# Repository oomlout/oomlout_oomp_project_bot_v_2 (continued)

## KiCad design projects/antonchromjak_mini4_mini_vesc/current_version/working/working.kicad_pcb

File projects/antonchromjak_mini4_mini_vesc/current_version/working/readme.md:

# mini4
 
## summary 
* id: antonchromjak_mini4_mini_vesc
* user: antonchromjak
* name: mini4
* board: mini_vesc
* repo: https://github.com/antonchromjak/MINI4
* src_file_repo_kicad_pcb: MINI VESC.kicad_pcb
* src_file_repo_kicad_pcb_link: https://github.com/antonchromjak/MINI4/tree/master/MINI VESC.kicad_pcb

* src_file_repo_sch: MINI VESC.sch
* src_file_repo_sch_link: https://github.com/antonchromjak/MINI4/tree/master/MINI VESC.sch
* full details link: https://github.com/oomlout/oomlout_oomp_project_bot_v_2/tree/main/projects/antonchromjak_mini4_mini_vesc/current_version/working  

## schematic  
  
[schematic (pdf)](working_schematic.pdf) 

## pcb  

[board (pdf)](working.pdf)  

## working_bom
| Id | Designator | Footprint | Quantity | Designation | Supplier and ref |  | None | 
| --- | --- | --- | --- | --- | --- | --- | --- | 
| 1 | U4,U5,U6 | MSOP | 3 | AD8418 |  |  | [''] | 
| 2 | C9,C10,C11,C17,C21,C77,C78,C22,C29,C6,C7,C8,C18,C19,C26,C27,C86,C87,C88,C89,C90 | C_0603 | 21 | 2u2 |  |  | [''] | 
| 3 | C14,C15,C16 | C_0603 | 3 | 4n7 |  |  | [''] | 
| 4 | R4,R12,R14,R16 | R_0603 | 4 | 25k5 |  |  | [''] | 
| 5 | R5,R13,R15,R17 | R_0603 | 4 | 2k2 |  |  | [''] | 
| 6 | R18,R19,R20,R30 | R_0603 | 4 | 100R |  |  | [''] | 
| 7 | C23 | R_0603 | 1 | 220nF |  |  | [''] | 
| 8 | C24,C25,C12,C13,C48,C28,C39,C60,C61,C62,C4,C5,C32,C63,C74,C75,C79,C82,C84,C85 | R_1206 | 20 | 10u |  |  | [''] | 
| 9 | D1 | D_SOD-123 | 1 | D_Schottky |  |  | [''] | 
| 10 | R21 | R_0603 | 1 | 510R |  |  | [''] | 
| 11 | R22 | R_0603 | 1 | 8k |  |  | [''] | 
| 12 | U8 | SOT-23-6 | 1 | LMR16006 |  |  | [''] | 
| 13 | P9,P10,P11 | JST_ZH_1.5_6-Pin | 3 | CONN_01X06 |  |  | [''] | 
| 14 | D3,D4 | R_0603 | 2 | LED |  |  | [''] | 
| 15 | R28,R29 | R_0603 | 2 | 220R |  |  | [''] | 
| 16 | C30,C31 | C_0603 | 2 | 10pF |  |  | [''] | 
| 17 | X1 | 5x3.2KRISTALL | 1 | CRYSTAL_SMD |  |  | [''] | 
| 18 | C34,C40,C42,C44,C45,C46,C47,C49,C50,C51,C52,C53,C54,C55,C56,C57,C58,C59,C64,C68,C69,C70,C71,C72,C73,C35,C36,C33,C37,C38,C41,C43,C65,C66,C67,C80,C81,C83 | R_1206 | 38 | C |  |  | [''] | 
| 19 | P1,P2,P3,P4,P5,P6 | prekov | 6 | CONN_1 |  |  | [''] | 
| 20 | R31,R33,R34 | R_0603 | 3 | 10k |  |  | [''] | 
| 21 | R32 | R_0603 | 1 | 10kNTC |  |  | [''] | 
| 22 | Q2,Q4,Q6,Q1,Q3,Q5 | DFN5 | 6 | Q_NMOS_GSD |  |  | [''] | 
| 23 | L1 | WE-MAPI | 1 | 22uH |  |  | [''] | 
| 24 | C1,C2,C3 | C_0603 | 3 | 220n |  |  | [''] | 
| 25 | U7 | lqfp64_pad_mod | 1 | STM32F40X_LQFP64 |  |  | [''] | 
| 26 | C20 | C_0603 | 1 | 220nF |  |  | [''] | 
| 27 | R6,R7,R8,R9,R10,R11 | R_0603 | 6 | 7R5 |  |  | [''] | 
| 28 | R25,R27 | R_0603 | 2 | 22R |  |  | [''] | 
| 29 | C76 | R_0603 | 1 | 100n |  |  | [''] | 
| 30 | U1,U2,U3 | WSON10_ | 3 | LM5113 |  |  | [''] | 
| 31 | R1,R2,R3 | 2512Rv2 | 3 | RSENS |  |  | [''] | 
| 32 | U9,U10 | SOT-23 | 2 | MCP1700 |  |  | [''] | 

## bom_schematic
| Ref | Qnty | Value | Cmp name | Footprint | Description | Vendor | DNP | 
| --- | --- | --- | --- | --- | --- | --- | --- | 
| L1 | 1 | Wurth Electronics 74438335220 | INDUCTOR-RESCUE-MINI_VESC | mojaKniznica:WE-MAPI |  |  |  | 
| P1, P2, P3, P4, P5, P6 | 6 | CONN_1 | CONN_1-RESCUE-MINI_VESC | kicad_subory:prekov |  |  |  | 
| R1, R2, R3 | 3 | R0005 | RSENS-RESCUE-MINI_VESC | mojaKniznica:2512Rv2 |  |  |  | 
| U1, U2, U3 | 3 | LM5113SDE | LM5001-RESCUE-MINI_VESC | kicad_subory:WSON10__ |  |  |  | 
| U4, U5, U6 | 3 | AD8417 | AD8418-RESCUE-MINI_VESC | kicad_subory:MSOP |  |  |  | 
| U7 | 1 | STM32F405RGT6 | STM32F40X_LQFP64-RESCUE-MINI_VESC | crf1:lqfp64_pad_mod |  |  |  | 
| U8 | 1 | LMR16006YDDCT | BD9G101G-RESCUE-MINI_VESC | TO_SOT_Packages_SMD:SOT-23-6 |  |  |  | 
| U9, U10 | 2 | MCP1700 | MCP1700-RESCUE-MINI_VESC | TO_SOT_Packages_SMD:SOT-23 |  |  |  | 
| X1 | 1 | ABM3B-8.000MHZ | CRYSTAL_SMD-RESCUE-MINI_VESC | mojaKniznica:5x3.2KRISTALL |  |  |  |

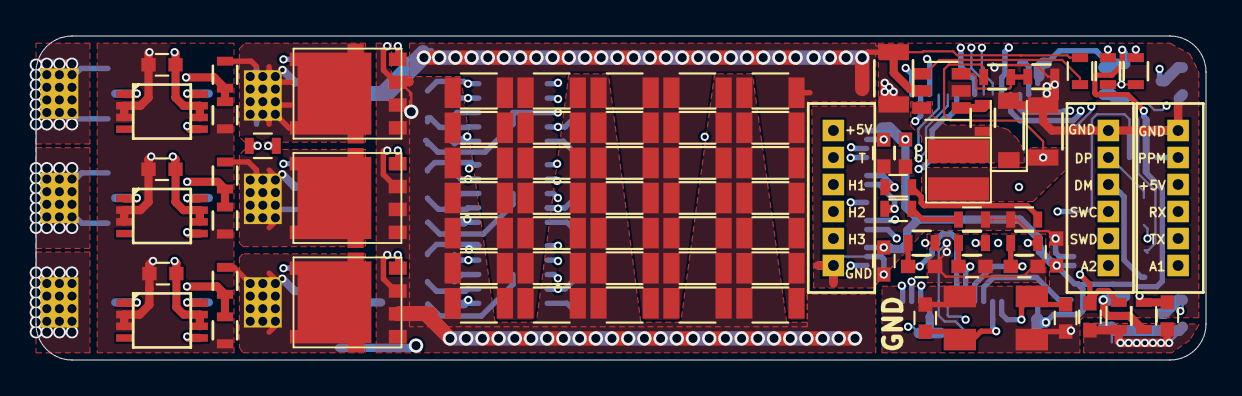
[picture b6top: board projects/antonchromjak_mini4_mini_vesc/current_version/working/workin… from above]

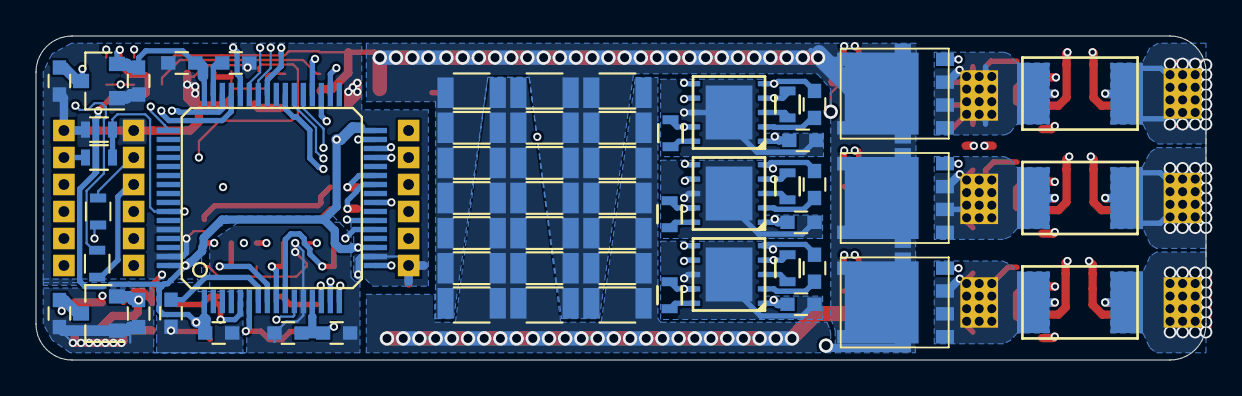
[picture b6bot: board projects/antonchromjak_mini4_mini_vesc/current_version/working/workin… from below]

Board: 4 copper layers, 65.0 x 18.0 mm, 151 parts (59 on the bottom side), 72 nets.

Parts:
C1, C2, C3: 220n; C_0603
C4, C5, C12, C13, C24, C25, C28, C32, C39, C48, C60, C61, C62, C63, C74, C75, C79, C82, C84, C85: 10u; R_1206
C6, C7, C8, C9, C10, C11, C17, C18, C19, C21, C22, C26, C27, C29, C77, C78, C86, C87, C88, C89, C90: 2u2; C_0603
C14, C15, C16: 4n7; C_0603
C20: 220nF; C_0603
C23: 220nF; R_0603
C30, C31: 10pF; C_0603
C33, C34, C35, C36, C37, C38, C40, C41, C42, C43, C44, C45, C46, C47, C49, C50, C51, C52, C53, C54, C55, C56, C57, C58, C59, C64, C65, C66, C67, C68, C69, C70, C71, C72, C73, C80, C81, C83: C; R_1206
C76: 100n; R_0603
D1: D_Schottky; D_SOD-123
D3, D4: LED; R_0603
L1: 22uH; WE-MAPI
P1, P2, P3, P4, P5, P6: CONN_1; prekov
P9, P10, P11: CONN_01X06; JST_ZH_1.5_6-Pin
Q1, Q2, Q3, Q4, Q5, Q6: Q_NMOS_GSD; DFN5
R1, R2, R3: RSENS; 2512Rv2
R4, R12, R14, R16: 25k5; R_0603
R5, R13, R15, R17: 2k2; R_0603
R6, R7, R8, R9, R10, R11: 7R5; R_0603
R18, R19, R20, R30: 100R; R_0603
R21: 510R; R_0603
R22: 8k; R_0603
R25, R27: 22R; R_0603
R28, R29: 220R; R_0603
R31, R33, R34: 10k; R_0603
R32: 10kNTC; R_0603
U1, U2, U3: LM5113; WSON10_
U4, U5, U6: AD8418; MSOP
U7: STM32F40X_LQFP64; lqfp64_pad_mod
U8: LMR16006; SOT-23-6
U9, U10: MCP1700; SOT-23
X1: CRYSTAL_SMD; 5x3.2KRISTALL

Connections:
+5V: C6.1, C7.1, C8.1, C25.2, C87.1, C89.1, L1.2, P9.1, P11.4, R22.1, U1.1, U2.1, U3.1, U9.3, U10.3
ADC_EXT1: P11.1, U7.21
ADC_EXT2: P10.1, U7.22
C1: C14.2, R18.2, U7.8
C2: C15.2, R19.2, U7.9
C3: C16.2, R20.2, U7.10
EN: R33.2, U8.4
HALL_1: P9.3, U7.37
HALL_2: P9.4, U7.38
HALL_3: P9.5, U7.39
HI1: U1.6, U7.41
HI2: U2.6, U7.42
HI3: U3.6, U7.43
I1: R18.1, U4.5
I2: R19.1, U5.5
I3: R20.1, U6.5
LED_GREEN: D3.2, U7.26
LED_RED: D4.2, U7.27
LI1: U1.7, U7.34
LI2: U2.7, U7.35
LI3: U3.7, U7.36
unnamed: C1.1, U1.2
unnamed: C2.1, U2.2
unnamed: C3.1, U3.2
unnamed: C17.2, U7.31
unnamed: C18.2, U7.47
unnamed: C20.2, U7.7
unnamed: C23.1, D1.1, L1.1, U8.6
unnamed: C23.2, U8.1
unnamed: C30.1, U7.5, X1.1
unnamed: C31.1, U7.6, X1.2
unnamed: C77.2, R31.2, R32.2, U7.17
unnamed: D3.1, R29.2
unnamed: D4.1, R28.2
unnamed: P1.1, R1.1, U4.1
unnamed: P2.1, R2.1, U5.1
unnamed: P3.1, R3.1, U6.1
unnamed: P10.4, R25.1
unnamed: P10.5, R27.1
unnamed: Q1.1, R6.1, U1.4
unnamed: Q2.1, R7.2, U1.9
unnamed: Q3.1, R8.1, U2.4
unnamed: Q4.1, R9.2, U2.9
unnamed: Q5.1, R10.1, U3.4
unnamed: Q6.1, R11.2, U3.9
unnamed: R6.2, U1.3
unnamed: R7.1, U1.10
unnamed: R8.2, U2.3
unnamed: R9.1, U2.10
unnamed: R10.2, U3.3
unnamed: R11.1, U3.10
unnamed: R21.2, R22.2, U8.3
RX: P11.3, U7.30
SENS_1: R12.1, R13.2, U7.14
SENS_2: R14.1, R15.2, U7.15
SENS_3: R16.1, R17.2, U7.16
SENS_SUPPLY: R4.2, R5.2, U7.11
SERVO: C76.2, R30.2, U7.58
SH1: C1.2, P4.1, Q1.2, Q2.3, R1.2, R12.2, U1.5, U4.8
SH2: C2.2, P5.1, Q3.2, Q4.3, R2.2, R14.2, U2.5, U5.8
SH3: C3.2, P6.1, Q5.2, Q6.3, R3.2, R16.2, U3.5, U6.8
SWCLK: P10.3, U7.49
SWDIO: P10.2, U7.46
TEMP_MOTOR: C78.2, P9.2, R34.2, U7.24
TX: P11.2, U7.29
USB-DM: R25.2, U7.44
USB-DP: R27.2, U7.45
VAA: C9.2, C10.2, C11.2, C19.1, C86.1, C90.1, R32.1, R34.1, U4.6, U4.7, U5.6, U5.7, U6.6, U6.7, U7.13, U10.2
VCC: C21.1, C22.1, C26.1, C27.1, C29.1, C88.1, U7.1, U7.19, U7.32, U7.48, U7.64, U9.2
VDD: C4.1, C5.1, C12.1, C13.1, C24.2, C28.1, C32.1, C33.1, C34.1, C35.1, C36.1, C37.1, C38.1, C39.1, C40.1, C41.1, C42.1, C43.1, C44.1, C45.1, C46.1, C47.1, C48.1, C49.1, C50.1, C51.1, C52.1, C53.1, C54.1, C55.1, C56.1, C57.1, C58.1, C59.1, C60.1, C61.1, C62.1, C63.1, C64.1, C65.1, C66.1, C67.1, C68.1, C69.1, C70.1, C71.1, C72.1, C73.1, C74.1, C75.1, C79.1, C80.1, C81.1, C82.1, C83.1, C84.1, C85.1, Q1.3, Q3.3, Q5.3, R4.1, R33.1, U8.5
VSS: C4.2, C5.2, C6.2, C7.2, C8.2, C9.1, C10.1, C11.1, C12.2, C13.2, C14.1, C15.1, C16.1, C17.1, C18.1, C19.2, C20.1, C21.2, C22.2, C24.1, C25.1, C26.2, C27.2, C28.2, C29.2, C30.2, C31.2, C32.2, C33.2, C34.2, C35.2, C36.2, C37.2, C38.2, C39.2, C40.2, C41.2, C42.2, C43.2, C44.2, C45.2, C46.2, C47.2, C48.2, C49.2, C50.2, C51.2, C52.2, C53.2, C54.2, C55.2, C56.2, C57.2, C58.2, C59.2, C60.2, C61.2, C62.2, C63.2, C64.2, C65.2, C66.2, C67.2, C68.2, C69.2, C70.2, C71.2, C72.2, C73.2, C74.2, C75.2, C76.1, C77.1, C78.1, C79.2, C80.2, C81.2, C82.2, C83.2, C84.2, C85.2, C86.2, C87.2, C88.2, C89.2, C90.2, D1.2, P9.6, P10.6, P11.6, Q2.2, Q4.2, Q6.2, R5.1, R13.1, R15.1, R17.1, R21.1, R28.1, R29.1, R31.1, U1.8, U2.8, U3.8, U4.2, U4.3, U5.2, U5.3, U6.2, U6.3, U7.12, U7.18, U7.60, U7.63, U8.2, U9.1, U10.1, X1.3
servoi: P11.5, R30.1

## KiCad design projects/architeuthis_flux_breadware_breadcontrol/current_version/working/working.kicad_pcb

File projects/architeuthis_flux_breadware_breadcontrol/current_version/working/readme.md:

# breadware
 
## summary 
* id: architeuthis_flux_breadware_breadcontrol
* user: architeuthis_flux
* name: breadware
* board: breadcontrol
* repo: https://github.com/Architeuthis-Flux/breadWare
* src_file_repo_kicad_pcb: v0.1-alpha/KiCad Files/BreadControl/BreadControl.kicad_pcb
* src_file_repo_kicad_pcb_link: https://github.com/Architeuthis-Flux/breadWare/tree/main/v0.1-alpha/KiCad Files/BreadControl/BreadControl.kicad_pcb
* src_file_repo_kicad_sch: Jumperless/Hardware/MTMatrixV3/MTMatrixV3.kicad_sch
* src_file_repo_kicad_sch_link: https://github.com/Architeuthis-Flux/breadWare/tree/main/Jumperless/Hardware/MTMatrixV3/MTMatrixV3.kicad_sch

* src_file_repo_sch: v0.1-alpha/KiCad Files/BreadControl/BreadControl.sch
* src_file_repo_sch_link: https://github.com/Architeuthis-Flux/breadWare/tree/main/v0.1-alpha/KiCad Files/BreadControl/BreadControl.sch
* full details link: https://github.com/oomlout/oomlout_oomp_project_bot_v_2/tree/main/projects/architeuthis_flux_breadware_breadcontrol/current_version/working  

## schematic  
  
[schematic (pdf)](working_schematic.pdf) 

## pcb  

[board (pdf)](working.pdf)  

## working_bom
| Id | Designator | Footprint | Quantity | Designation | Supplier and ref |  | None | 
| --- | --- | --- | --- | --- | --- | --- | --- | 
| 1 | C1 | C_0805_2012Metric_Pad1.15x1.40mm_HandSolder | 1 | 1uF |  |  | [''] | 
| 2 | C2,C4,C6,C7 | C_0805_2012Metric_Pad1.15x1.40mm_HandSolder | 4 | 10uF |  |  | [''] | 
| 3 | C3,C5 | C_0805_2012Metric_Pad1.15x1.40mm_HandSolder | 2 | 4.7uF |  |  | [''] | 
| 4 | D1 | D_0603_1608Metric_Pad1.05x0.95mm_HandSolder | 1 | Rx |  |  | [''] | 
| 5 | D2 | D_0603_1608Metric_Pad1.05x0.95mm_HandSolder | 1 | Tx |  |  | [''] | 
| 6 | D3 | D_0603_1608Metric_Pad1.05x0.95mm_HandSolder | 1 | USB |  |  | [''] | 
| 7 | D4 | D_0603_1608Metric_Pad1.05x0.95mm_HandSolder | 1 | I2C |  |  | [''] | 
| 8 | D5,D6 | D_SOD-323_HandSoldering | 2 | D_Schottky_Small |  |  | [''] | 
| 9 | J1 | PinHeader_1x16_P2.54mm_Vertical | 1 | Address_Control_Power |  |  | [''] | 
| 10 | J2 | PinHeader_1x16_P2.54mm_Vertical | 1 | Chip_Select_Measurement |  |  | [''] | 
| 11 | J3 | PinHeader_1x03_P2.54mm_Vertical | 1 | UPDI |  |  | [''] | 
| 12 | L1,L2 | L_1008_2520Metric | 2 | 10uH |  |  | [''] | 
| 13 | M1,M2 | SOT-23-5_HandSoldering | 2 | ZXLD1615 |  |  | [''] | 
| 14 | PS1 | CONV_DPU01L-05 | 1 | DPU01L-05 |  |  | [''] | 
| 15 | R1,R2,R5,R11 | R_0805_2012Metric_Pad1.15x1.40mm_HandSolder | 4 | 220R |  |  | [''] | 
| 16 | R3,R4 | R_0805_2012Metric_Pad1.15x1.40mm_HandSolder | 2 | 10K |  |  | [''] | 
| 17 | R12,R16,R17,R20 | R_0805_2012Metric_Pad1.15x1.40mm_HandSolder | 4 | 56.2K |  |  | [''] | 
| 18 | R13,R21 | R_0805_2012Metric_Pad1.15x1.40mm_HandSolder | 2 | 91K |  |  | [''] | 
| 19 | R14,R18,R19,R22 | R_0805_2012Metric_Pad1.15x1.40mm_HandSolder | 4 | 14K |  |  | [''] | 
| 20 | R15,R23 | R_0805_2012Metric_Pad1.15x1.40mm_HandSolder | 2 | 1M |  |  | [''] | 
| 21 | U1 | SOIC-14_3.9x8.7mm_P1.27mm | 1 | MCP2221A-I_SL |  |  | [''] | 
| 22 | U2 | PLCC-44_16.6x16.6mm_P1.27mm | 1 | MT8816AP |  |  | [''] | 
| 23 | U3 | TQFP-48_7x7mm_P0.5mm | 1 | ATmega4809-A |  |  | [''] | 
| 24 | U4 | TSSOP-14_4.4x5mm_P0.65mm | 1 | MCP4661-104E_ST |  |  | [''] | 
| 25 | J4 | AMPHENOL_10033526-N3212LF | 1 | USB_B_Mini |  |  | [''] | 

## bom_schematic
| Ref | Qnty | Value | Cmp name | Footprint | Description | Vendor | DNP | 
| --- | --- | --- | --- | --- | --- | --- | --- | 
| C1 | 1 | 1uF | C_Small | Capacitor_SMD:C_0805_2012Metric_Pad1.15x1.40mm_HandSolder | Unpolarized capacitor, small symbol |  |  | 
| C2, C4, C6, C7 | 4 | 10uF | C_Small | Capacitor_SMD:C_0805_2012Metric_Pad1.15x1.40mm_HandSolder | Unpolarized capacitor, small symbol |  |  | 
| C3, C5 | 2 | 4.7uF | C_Small | Capacitor_SMD:C_0805_2012Metric_Pad1.15x1.40mm_HandSolder | Unpolarized capacitor, small symbol |  |  | 
| D1 | 1 | Rx | LED_Small | Diode_SMD:D_0603_1608Metric_Pad1.05x0.95mm_HandSolder | Light emitting diode, small symbol |  |  | 
| D2 | 1 | Tx | LED_Small | Diode_SMD:D_0603_1608Metric_Pad1.05x0.95mm_HandSolder | Light emitting diode, small symbol |  |  | 
| D3 | 1 | USB | LED_Small | Diode_SMD:D_0603_1608Metric_Pad1.05x0.95mm_HandSolder | Light emitting diode, small symbol |  |  | 
| D4 | 1 | I2C | LED_Small | Diode_SMD:D_0603_1608Metric_Pad1.05x0.95mm_HandSolder | Light emitting diode, small symbol |  |  | 
| D5, D6 | 2 | D_Schottky_Small | D_Schottky_Small | Diode_SMD:D_SOD-323_HandSoldering | Schottky diode, small symbol |  |  | 
| J1 | 1 | Address_Control_Power | Conn_01x16_Female-Connector | Connector_PinHeader_2.54mm:PinHeader_1x16_P2.54mm_Vertical |  |  |  | 
| J2 | 1 | Chip_Select_Measurement | Conn_01x16_Female-Connector | Connector_PinHeader_2.54mm:PinHeader_1x16_P2.54mm_Vertical |  |  |  | 
| J3 | 1 | UPDI | Conn_01x03_Male-Connector | Connector_PinHeader_2.54mm:PinHeader_1x03_P2.54mm_Vertical |  |  |  | 
| J4 | 1 | USB_B_Mini | USB_B_Mini-Connector | 10033526-N3212LF:AMPHENOL_10033526-N3212LF |  |  |  | 
| L1, L2 | 2 | 10uH | L_Small | Inductor_SMD:L_1008_2520Metric | Inductor, small symbol |  |  | 
| M1, M2 | 2 | ZXLD1615 | ZXLD1615-Regulator_Controller | Package_TO_SOT_SMD:SOT-23-5_HandSoldering |  |  |  | 
| PS1 | 1 | DPU01L-05 | DPU01L-05-DPU01L-05 | DPU01L-05:CONV_DPU01L-05 |  |  |  | 
| R1, R2, R5, R11 | 4 | 220R | R_Small_US | Resistor_SMD:R_0805_2012Metric_Pad1.15x1.40mm_HandSolder | Resistor, small US symbol |  |  | 
| R3, R4 | 2 | 10K | R_Small_US | Resistor_SMD:R_0805_2012Metric_Pad1.15x1.40mm_HandSolder | Resistor, small US symbol |  |  | 
| R12, R16, R17, R20 | 4 | 56.2K | R_Small_US | Resistor_SMD:R_0805_2012Metric_Pad1.15x1.40mm_HandSolder | Resistor, small US symbol |  |  | 
| R13, R21 | 2 | 91K | R_Small_US | Resistor_SMD:R_0805_2012Metric_Pad1.15x1.40mm_HandSolder | Resistor, small US symbol |  |  | 
| R14, R18, R19, R22 | 4 | 14K | R_Small_US | Resistor_SMD:R_0805_2012Metric_Pad1.15x1.40mm_HandSolder | Resistor, small US symbol |  |  | 
| R15, R23 | 2 | 1M | R_Small_US | Resistor_SMD:R_0805_2012Metric_Pad1.15x1.40mm_HandSolder | Resistor, small US symbol |  |  | 
| U1 | 1 | MCP2221A-I_SL | MCP2221A-I_SL-MCP2221A-I_SL | Package_SO:SOIC-14_3.9x8.7mm_P1.27mm |  |  |  | 
| U2 | 1 | MT8816AP | MT8816AP-MT8816 | Package_LCC:PLCC-44_16.6x16.6mm_P1.27mm |  |  |  | 
| U3 | 1 | ATmega4809-A | ATmega4809-A | Package_QFP:TQFP-48_7x7mm_P0.5mm | 20MHz, 48kB Flash, 6kB SRAM, 256B EEPROM, TQFP-48 |  |  | 
| U4 | 1 | MCP4661-104E_ST | MCP4661-104E_ST-MCP4661-104E_ST | Package_SO:TSSOP-14_4.4x5mm_P0.65mm |  |  |  |

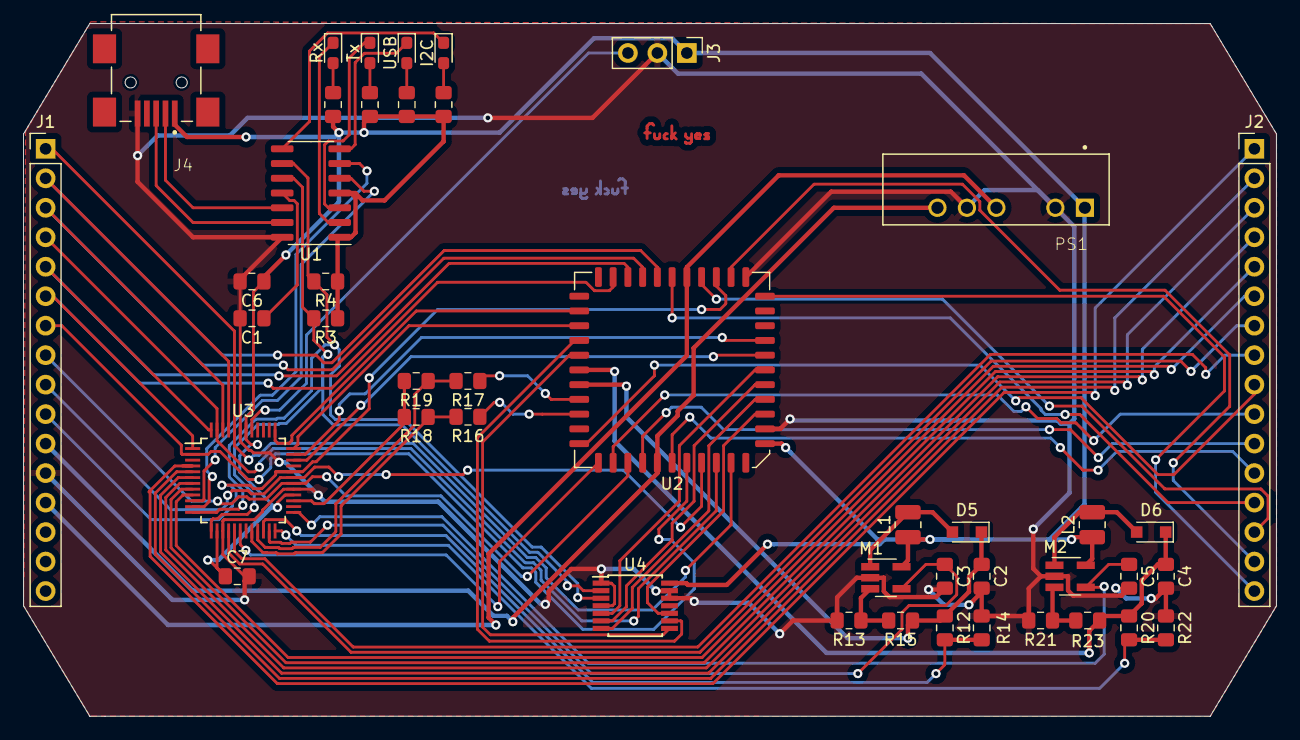
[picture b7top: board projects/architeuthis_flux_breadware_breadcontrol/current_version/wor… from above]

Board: 2 copper layers, 108.0 x 59.7 mm, 44 parts (0 on the bottom side), 72 nets.

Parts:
C1: 1uF; C_0805_2012Metric_Pad1.15x1.40mm_HandSolder
C2, C4, C6, C7: 10uF; C_0805_2012Metric_Pad1.15x1.40mm_HandSolder
C3, C5: 4.7uF; C_0805_2012Metric_Pad1.15x1.40mm_HandSolder
D1: Rx; D_0603_1608Metric_Pad1.05x0.95mm_HandSolder
D2: Tx; D_0603_1608Metric_Pad1.05x0.95mm_HandSolder
D3: USB; D_0603_1608Metric_Pad1.05x0.95mm_HandSolder
D4: I2C; D_0603_1608Metric_Pad1.05x0.95mm_HandSolder
D5, D6: D_Schottky_Small; D_SOD-323_HandSoldering
J1: Address_Control_Power; PinHeader_1x16_P2.54mm_Vertical
J2: Chip_Select_Measurement; PinHeader_1x16_P2.54mm_Vertical
J3: UPDI; PinHeader_1x03_P2.54mm_Vertical
J4: USB_B_Mini; AMPHENOL_10033526-N3212LF
L1, L2: 10uH; L_1008_2520Metric
M1, M2: ZXLD1615; SOT-23-5_HandSoldering
PS1: DPU01L-05; CONV_DPU01L-05
R1, R2, R5, R11: 220R; R_0805_2012Metric_Pad1.15x1.40mm_HandSolder
R3, R4: 10K; R_0805_2012Metric_Pad1.15x1.40mm_HandSolder
R12, R16, R17, R20: 56.2K; R_0805_2012Metric_Pad1.15x1.40mm_HandSolder
R13, R21: 91K; R_0805_2012Metric_Pad1.15x1.40mm_HandSolder
R14, R18, R19, R22: 14K; R_0805_2012Metric_Pad1.15x1.40mm_HandSolder
R15, R23: 1M; R_0805_2012Metric_Pad1.15x1.40mm_HandSolder
U1: MCP2221A-I_SL; SOIC-14_3.9x8.7mm_P1.27mm
U2: MT8816AP; PLCC-44_16.6x16.6mm_P1.27mm
U3: ATmega4809-A; TQFP-48_7x7mm_P0.5mm
U4: MCP4661-104E_ST; TSSOP-14_4.4x5mm_P0.65mm

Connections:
0: J2.9, U2.39
8: J2.10, U2.41
16: J2.11, U2.43
24: J2.12, U2.1
32: J2.13, U2.23
40: J2.14, U2.21
48: J2.15, U2.19
56: J2.16, U2.17
+5V: C6.1, C7.1, J3.1, J4.1, L1.1, L2.1, M1.5, M2.5, PS1.1, R1.1, R2.1, R3.1, R4.1, R5.1, R11.1, U1.1, U1.4, U2.7, U3.14, U3.28, U3.42, U4.14
+9V: J1.11, PS1.6, U2.44
-9V: J1.13, PS1.4, U2.22
AX0: J1.1, U2.5, U3.44
AX1: J1.2, U2.24, U3.45
AX2: J1.3, U2.25, U3.46
AX3: J1.4, U2.4, U3.47
AY0: J1.5, U2.26, U3.48
AY1: J1.6, U2.27, U3.1
AY2: J1.7, U2.2, U3.2
CS_A: J2.1, U3.4
CS_B: J2.2, U3.5
CS_C: J2.3, U3.6
CS_D: J2.4, U3.7
CS_E: J2.5, U3.8
CS_F: J2.6, U3.9
CS_G: J2.7, U3.16
CS_H: J2.8, U3.17
CS_I: U2.40, U3.18
DATA: J1.8, U2.42, U3.30
GND: C1.2, C2.2, C3.2, C4.2, C5.2, C6.2, C7.2, J1.12, J3.2, J4.5, M1.2, M2.2, PS1.2, PS1.5, R13.1, R14.2, R21.1, R22.2, U1.14, U2.8, U2.18, U3.15, U3.29, U3.43, U4.1, U4.4, U4.12, U4.13
I2C_SCL: R3.2, U1.10, U3.13, U4.2
I2C_SDA: R4.2, U1.9, U3.12, U4.3
unnamed: C1.1, U1.11
unnamed: D1.1, U1.2
unnamed: D1.2, R1.2
unnamed: D2.1, U1.3
unnamed: D2.2, R2.2
unnamed: D3.1, U1.7
unnamed: D3.2, R5.2
unnamed: D4.1, U1.8
unnamed: D4.2, R11.2
unnamed: D5.2, L1.2, M1.1
unnamed: D6.2, L2.2, M2.1
unnamed: J3.3, U3.41
unnamed: M1.3, R13.2, R15.1
unnamed: M2.3, R21.2, R23.1
PF0: U2.13, U3.34
PF1: U2.14, U3.35
PF2: U2.31, U3.36
PF3: U2.30, U3.37
POT0_A: U2.33, U4.8
POT0_B: U2.9, U4.10
POT0_W: U2.32, U4.9
POT1_A: U2.10, U4.7
POT1_B: U2.12, U4.5
POT1_W: U2.11, U4.6
RESET: J1.9, U2.3, U3.31
STROBE: J1.10, U2.20, U3.32
USB_D+: J4.3, U1.13
USB_D-: J4.2, U1.12
USB_Rx: U1.5, U3.10
USB_Tx: U1.6, U3.11
VDIV_0: R16.2, R18.1, U3.20
VDIV_1: R17.2, R19.1, U3.21
VREF_ADC_BIAS: R18.2, R19.2, U3.27
X0_ADC: R16.1, U2.37
X1_ADC: R17.1, U2.36
ZXLD1_EN: C3.1, M1.4, U3.23
ZXLD1_SENSE: R12.2, R14.1, U3.22
ZXLD1_VOUT: C2.1, D5.1, R12.1, R15.2, U2.35
ZXLD2_EN: C5.1, M2.4, U3.25
ZXLD2_SENSE: R20.2, R22.1, U3.24
ZXLD2_VOUT: C4.1, D6.1, R20.1, R23.2, U2.34
